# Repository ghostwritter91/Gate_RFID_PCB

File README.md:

1. Gate opening via RFID (13,56 MHz)
2. ESP8266 + MFRC522

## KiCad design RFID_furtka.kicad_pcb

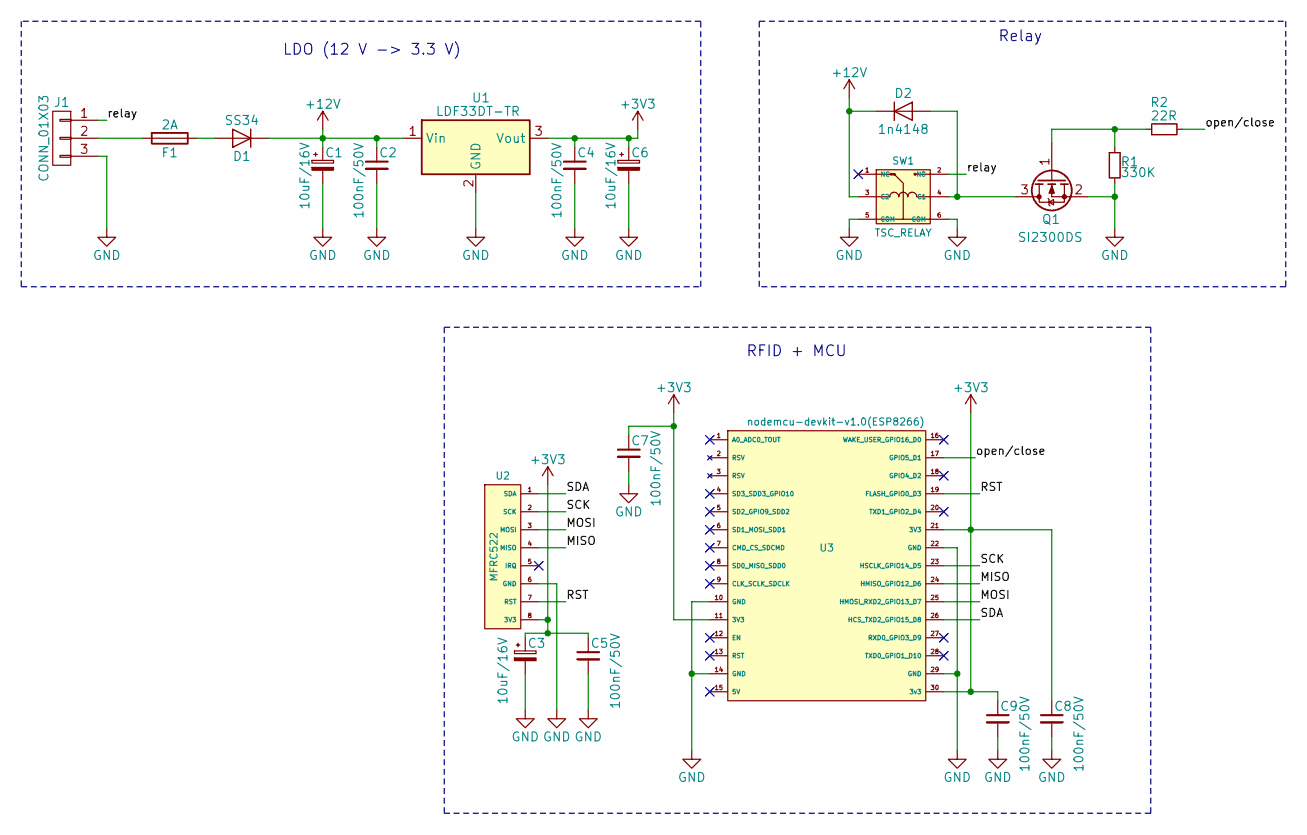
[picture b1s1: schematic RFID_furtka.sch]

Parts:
C1, C3, C6: 10uF/16V; C_1611
C2, C4, C5, C7, C8, C9: 100nF/50V; C_0805_HandSoldering
D1: SS34; D_SMA_Handsoldering
D2: 1n4148; D_DO-35_SOD27_P10.16mm_Horizontal
F1: 2A; R_0805_HandSoldering
J1: CONN_01X03; KF141R-2.54-3P
Q1: SI2300DS; SOT-23
R1: 330K; R_0805_HandSoldering
R2: 22R; R_0603_HandSoldering
SW1: TSC_RELAY; TSC-1XXX
U1: LDF33DT-TR; DPAK
U2: MFRC522; MRFCC522
U3: nodemcu-devkit-v1.0(ESP8266); nodemcu1.0

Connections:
+3V3: C3.1, C4.1, C5.1, C6.1, C7.1, C8.1, C9.1, U1.3 (Vout), U2.8 (3V3), U3.11 (3V3), U3.21 (3V3), U3.30 (3v3)
+12V: C1.1, C2.1, D1.1 (K), D2.1 (K), SW1.3 (C2), U1.1 (Vin)
/MISO: U2.4 (MISO), U3.24 (HMISO_GPIO12_D6)
/MOSI: U2.3 (MOSI), U3.25 (HMOSI_RXD2_GPIO13_D7)
/RST: U2.7 (RST), U3.19 (FLASH_GPIO0_D3)
/SCK: U2.2 (SCK), U3.23 (HSCLK_GPIO14_D5)
/SDA: U2.1 (SDA), U3.26 (HCS_TXD2_GPIO15_D8)
/open/close: R2.2, U3.17 (GPIO5_D1)
/relay: J1.1, SW1.2 (NO)
GND: C1.2, C2.2, C3.2, C4.2, C5.2, C6.2, C7.2, C8.2, C9.2, J1.3, Q1.2 (S), R1.2, SW1.5 (COM), SW1.6 (COM), U1.2 (GND), U2.6 (GND), U3.10 (GND), U3.14 (GND), U3.22 (GND), U3.29 (GND)
unnamed: D1.2 (A), F1.1
unnamed: D2.2 (A), Q1.3 (D), SW1.4 (C1)
unnamed: F1.2, J1.2
unnamed: Q1.1 (G), R1.1, R2.1

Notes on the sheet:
LDO (12 V -> 3.3 V)
Relay
RFID + MCU

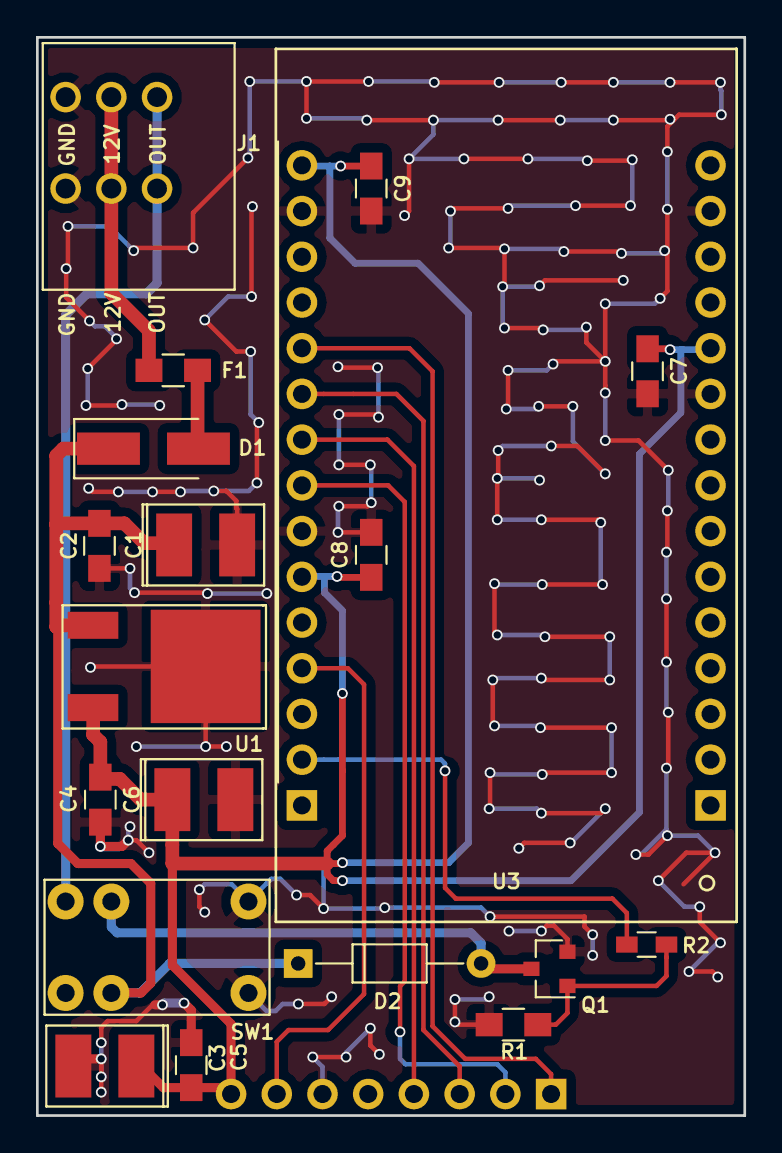
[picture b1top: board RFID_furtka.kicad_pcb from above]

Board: 2 copper layers, 39.3 x 59.9 mm, 20 parts (1 on the bottom side), 14 nets.

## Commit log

2017-11-19 Add LDO, Relay, ESP and MRFCC522
2017-12-16 All components
2017-12-27 First PCB
2017-12-28 Add BOM
2017-12-28 Fix few 3D bugs
2017-12-28 Fix edge cuts
2017-12-31 All signals routed without GND
2018-01-07 Add GND vias
2018-01-14 Add some comments and production files
2018-02-03 Final version
2018-05-04 Add comments about relay
